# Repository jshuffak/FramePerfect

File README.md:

# FramePerfect
Code for using a Freescale 9S12C32 to intercept a GameCube controller's signal and replace it with a macro.

Project demonstration video is coming soon.

Code is contained in the folder: Gamecube_Project_Triggered/Sources/

Hardware code is contained in the folder: Output Test/GAL/ 

Special thanks to team members Kyle Diekhoff, Eric Colter, and Diego De La Fuente for pulling this one off and placing 2nd place in the Purdue Spark Challenge.

See https://engineering.purdue.edu/ECESS/spark/ for more information about the bi-annual competition hosted at Purdue University.

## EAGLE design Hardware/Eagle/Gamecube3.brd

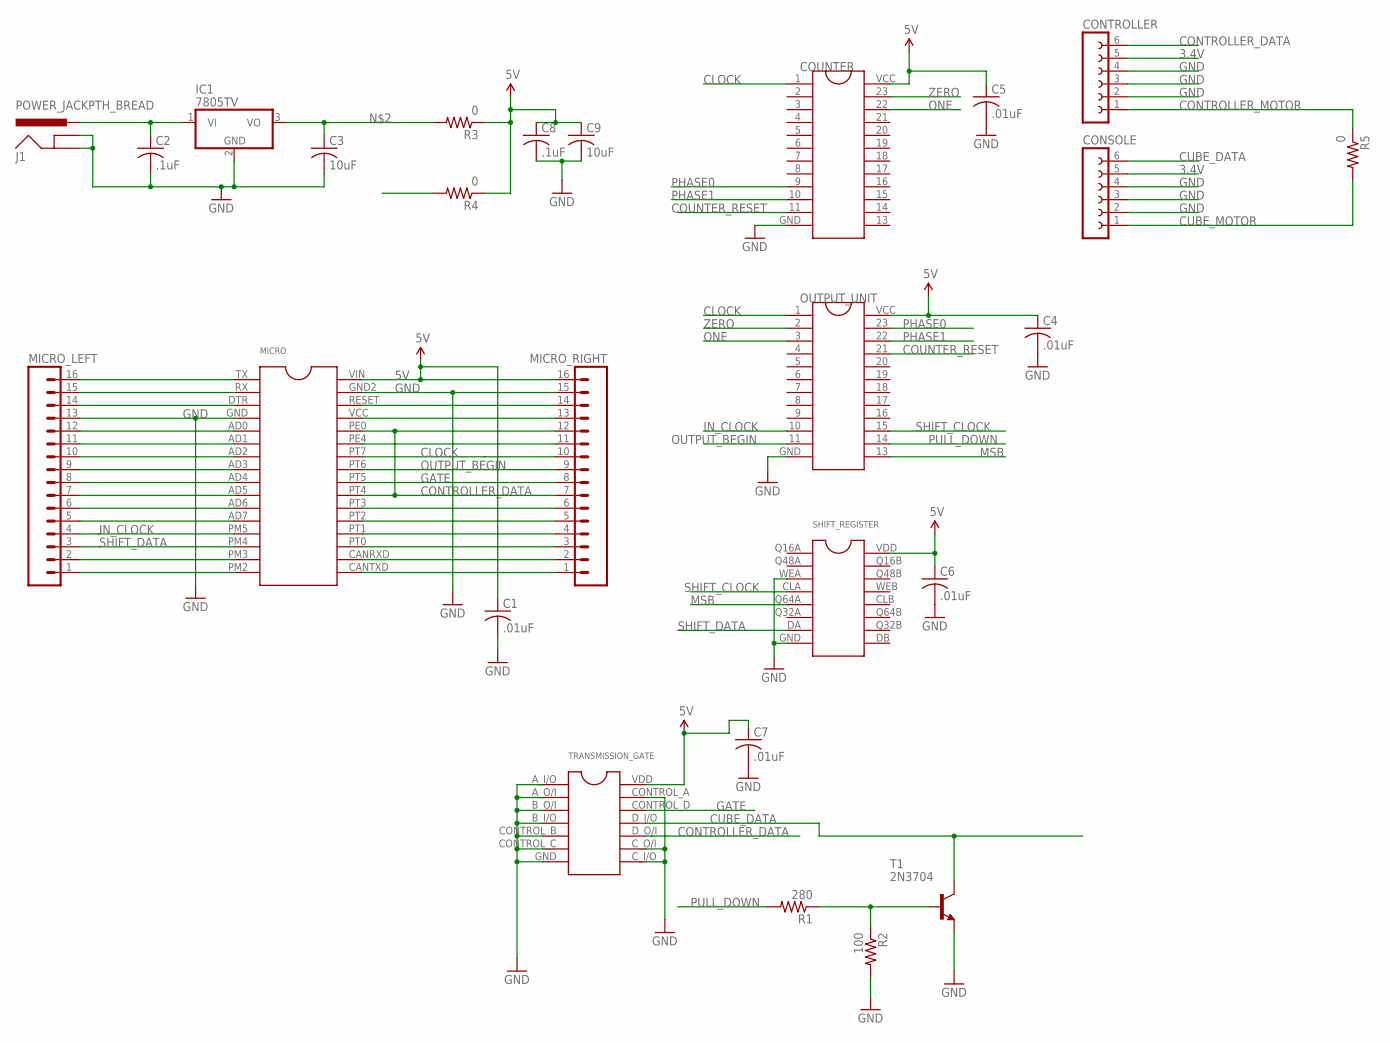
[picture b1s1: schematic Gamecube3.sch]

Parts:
C1, C4, C5, C6, C7: .01uF; C0805
C2, C8: .1uF; C0805
C3, C9: 10uF; C1206
CONSOLE: FE06-1; FE06
CONTROLLER: FE06-1; FE06
COUNTER: GAL22V10; 24-PIN-DIP
IC1: 7805TV; TO220V
J1: POWER_JACKPTH_BREAD; POWER_JACK_PTH_BREAD
MICRO: 9S12C32; 9S12-32PIN-DIP
MICRO_LEFT: M16; 16P
MICRO_RIGHT: M16; 16P
OUTPUT_UNIT: GAL22V10; 24-PIN-DIP
R1: 280; 0204/7
R2: 100; 0204/7
R3, R4, R5: 0; 0204/7
SHIFT_REGISTER: CD4517B
T1: 2N3704; TO92
TRANSMISSION_GATE: CD4066B

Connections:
3.4V: CONSOLE.5, CONTROLLER.5
5V: C1.1, C4.1, C5.1, C6.1, C7.1, C8.1, C9.1, COUNTER.VCC, MICRO.VIN, MICRO_RIGHT.16, OUTPUT_UNIT.VCC, R3.1, R4.1, SHIFT_REGISTER.VDD, TRANSMISSION_GATE.VDD
CLOCK: COUNTER.1, MICRO.PT7, MICRO_RIGHT.10, OUTPUT_UNIT.1
CONTROLLER_DATA: CONTROLLER.6, MICRO.PE0, MICRO.PT4, MICRO_RIGHT.7, MICRO_RIGHT.12, TRANSMISSION_GATE.D_O/I
CONTROLLER_MOTOR: CONTROLLER.1, R5.1
COUNTER_RESET: COUNTER.11, OUTPUT_UNIT.21
CUBE_DATA: CONSOLE.6, T1.2 (C), TRANSMISSION_GATE.D_I/O
CUBE_MOTOR: CONSOLE.1, R4.2, R5.2
GATE: MICRO.PT5, MICRO_RIGHT.8, TRANSMISSION_GATE.CONTROL_D
GND: C1.2, C2.2, C3.2, C4.2, C5.2, C6.2, C7.2, C8.2, C9.2, CONSOLE.2, CONSOLE.3, CONSOLE.4, CONTROLLER.2, CONTROLLER.3, CONTROLLER.4, COUNTER.GND, IC1.2 (GND), J1.GND, J1.GNDBREAK, MICRO.GND, MICRO.GND2, MICRO_LEFT.13, MICRO_RIGHT.15, OUTPUT_UNIT.GND, R2.2, SHIFT_REGISTER.GND, SHIFT_REGISTER.WEA, T1.3 (E), TRANSMISSION_GATE.A_I/O, TRANSMISSION_GATE.A_O/I, TRANSMISSION_GATE.B_I/O, TRANSMISSION_GATE.B_O/I, TRANSMISSION_GATE.CONTROL_A, TRANSMISSION_GATE.CONTROL_B, TRANSMISSION_GATE.CONTROL_C, TRANSMISSION_GATE.C_I/O, TRANSMISSION_GATE.C_O/I, TRANSMISSION_GATE.GND
IN_CLOCK: MICRO.PM5, MICRO_LEFT.4, OUTPUT_UNIT.10
MSB: OUTPUT_UNIT.13, SHIFT_REGISTER.Q64A
unnamed: C2.1, IC1.1 (VI), J1.PWR
unnamed: C3.1, IC1.3 (VO), R3.2
unnamed: R1.1, R2.1, T1.1 (B)
unnamed: MICRO.CANTXD, MICRO_RIGHT.1
unnamed: MICRO.PM2, MICRO_LEFT.1
unnamed: MICRO.PM3, MICRO_LEFT.2
unnamed: MICRO.AD7, MICRO_LEFT.5
unnamed: MICRO.AD6, MICRO_LEFT.6
unnamed: MICRO.AD5, MICRO_LEFT.7
unnamed: MICRO.AD4, MICRO_LEFT.8
unnamed: MICRO.AD3, MICRO_LEFT.9
unnamed: MICRO.AD2, MICRO_LEFT.10
unnamed: MICRO.AD1, MICRO_LEFT.11
unnamed: MICRO.AD0, MICRO_LEFT.12
unnamed: MICRO.DTR, MICRO_LEFT.14
unnamed: MICRO.RX, MICRO_LEFT.15
unnamed: MICRO.TX, MICRO_LEFT.16
unnamed: MICRO.CANRXD, MICRO_RIGHT.2
unnamed: MICRO.PT0, MICRO_RIGHT.3
unnamed: MICRO.PT1, MICRO_RIGHT.4
unnamed: MICRO.PT2, MICRO_RIGHT.5
unnamed: MICRO.PT3, MICRO_RIGHT.6
unnamed: MICRO.PE4, MICRO_RIGHT.11
unnamed: MICRO.VCC, MICRO_RIGHT.13
unnamed: MICRO.RESET, MICRO_RIGHT.14
ONE: COUNTER.22, OUTPUT_UNIT.3
OUTPUT_BEGIN: MICRO.PT6, MICRO_RIGHT.9, OUTPUT_UNIT.11
PHASE0: COUNTER.9, OUTPUT_UNIT.23
PHASE1: COUNTER.10, OUTPUT_UNIT.22
PULL_DOWN: OUTPUT_UNIT.14, R1.2
SHIFT_CLOCK: OUTPUT_UNIT.15, SHIFT_REGISTER.CLA
SHIFT_DATA: MICRO.PM4, MICRO_LEFT.3, SHIFT_REGISTER.DA
ZERO: COUNTER.23, OUTPUT_UNIT.2

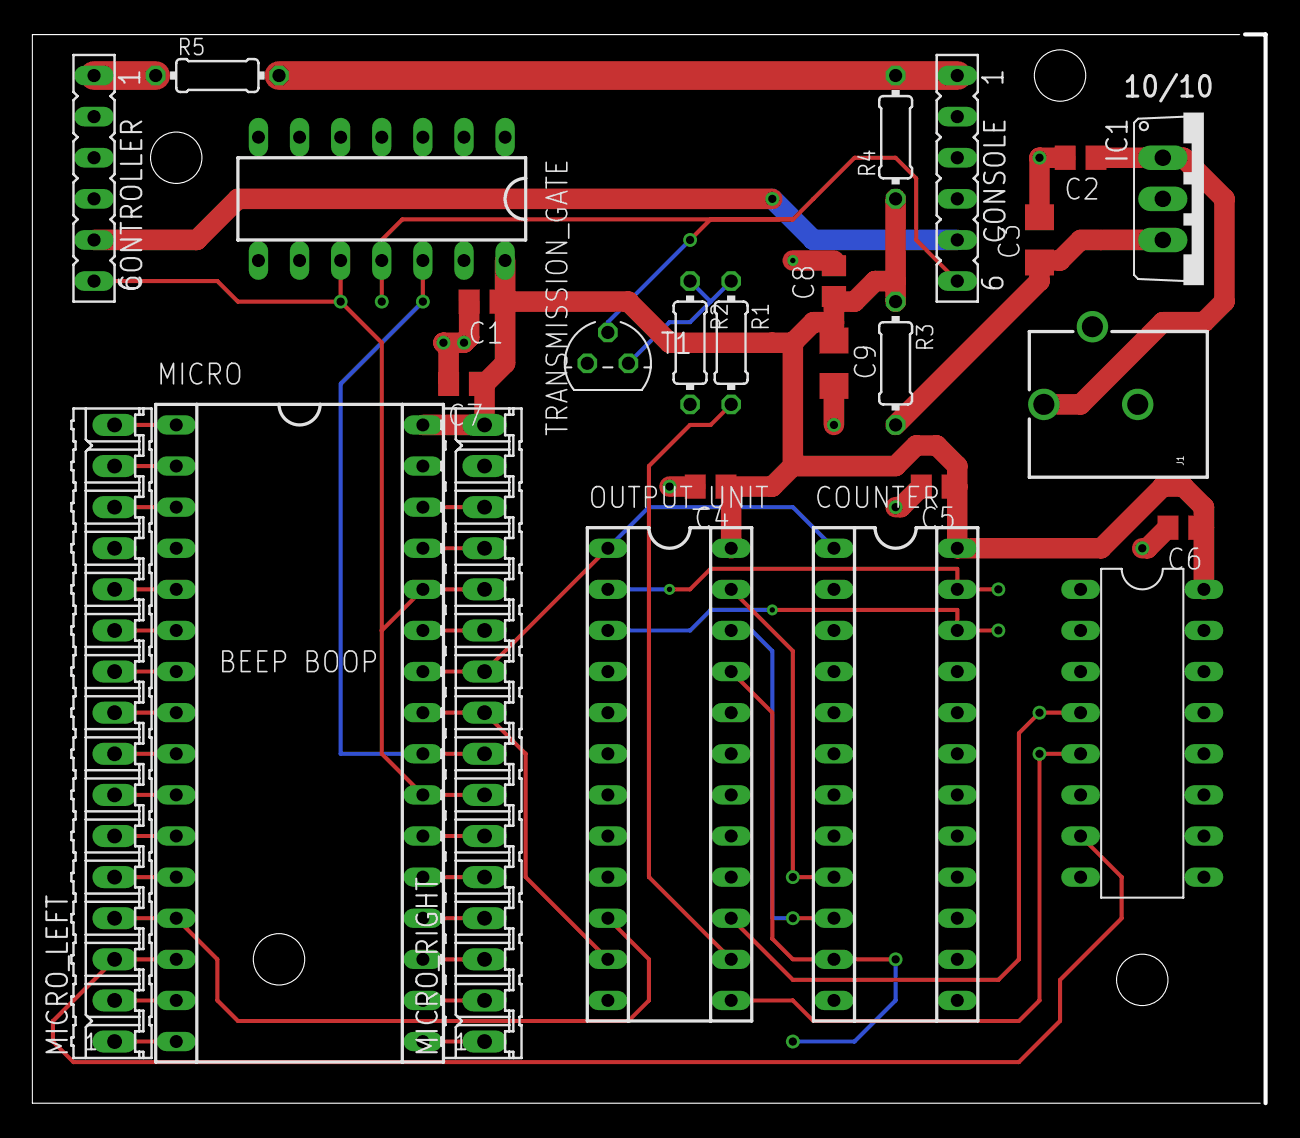
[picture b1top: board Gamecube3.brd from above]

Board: 2 copper layers, 76.1 x 66.0 mm, 26 parts (0 on the bottom side), 45 nets.

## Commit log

2015-11-21 Added some sample structure files to the repo.
2015-11-26 A whole bunch of stuff. Neat!
2015-12-04 Added some GAL stuff and also the working echo program.
2015-12-04 Added all necessary files to the repo and added them to the CodeWarrior project.
2015-12-04 Added some initializations and finished macro.h
2015-12-04 Changed some stuff
2015-12-04 Changed some more stuff aparently
2015-12-04 Added functions to microcontroller.h that are needed by other modules
2015-12-05 changes to the code warrior project i dont actually want to keep.
2015-12-05 Update macro.c
    Kyle did the best job ever made in the world
2015-12-05 Change define
    Rickster the fan man
2015-12-05 Added equals sign for macro
2015-12-05 Update macro.h
    Fixed macro.h
2015-12-05 Finished the definitions of the .h files and some definitions in the .c files.
2015-12-05 Changed Structure to multi macro
2015-12-05 The horrible length update
2015-12-05 Added defined start of each macro
2015-12-05 Changed scheme.h to not have definitions of each scheme and moved them to scheme.c.
2015-12-05 Update microcontroller.c
    - Changes to line up controller/console output with IRQ and to make sure that it's length of time was good.
2015-12-05 Finished main.
2015-12-05 Added scheme.c to the codewarrior project and fixed a bug to let it compile.
2015-12-05 Shut up nerd
2015-12-05 fox jump
2015-12-05 Tested Kyle's Code with control.h functionality and it seems to work. Also reconfigured scheme1 to use some niftey macros.
2015-12-05 Forgot to change back the changes I made to test.
2015-12-05 Changed CYCLESFOR40MICROWAIT to ensure that the micro is waiting 40 microseconds.
2015-12-05 Added Kyle's Macro generator into the repo.
2015-12-05 Added Colter's work into the repo.
2015-12-07 Updated the repo with the merged changes from Colter and Diego's work.
2015-12-07 Fixed a bug in the macro.c file.
2015-12-07 Changed the routine to mask the left and right slider values when the macro button is pressed.
2015-12-07 Now masks the x and y joystick values when the macro button is pressed unless they cross the x and y thresholds.
2015-12-07 Changed the thresholds to be a snappier value.
2015-12-07 Added a watchdog timer to the micro to ensure that the protocol is working properly.
2015-12-07 Refixed a debugging problem and added an initial state of input.
2015-12-07 Change initial bit
    ye
2015-12-07 do you have the time to listen to me whine.
2015-12-07 4 scores and seven years ago our founding fathers
    did stuff
2015-12-07 Schemes are updated
2015-12-07 Updated initial bits sent to GAL
    Updated the initial bits to be blank inputs so that the GAL doesn't output garbage initially.
2015-12-07 True to its name
2015-12-07 12/7/2015: Updated and Added Macros
2015-12-07 Update and Added Macros 12/7/2015
2015-12-07 12/7/2015: Updated and Added Schemes
2015-12-08 Assert macro frames 2 times
    Changed the macro so that each frame is asserted 2 times instead of 3.
2015-12-08 Updated a couple of macros
    Updated some macros with the new 2 input frame per game frame protocol.
2015-12-08 Updated some more macros
    Updated some macros with new sizes.
2015-12-08 Added masks to the joystick
2015-12-08 updated macro.c to have macros. limited RAM
2015-12-08 updated macro.h 12/8/2015 1:21 am. limited RAM
2015-12-08 Using flash memory?
    Hopefully using flash memory now.
2015-12-09 Added drillshine. Test1
2015-12-09 added drillshine to scheme1 x-z
2015-12-09 updated drillshine macro8
2015-12-09 update macro.h for drill
2015-12-09 DRILL 2
2015-12-09 DRILL2
2015-12-09 DRILL 3
2015-12-09 Commiting broken DrillShine
    Broken drill shine
2015-12-09 final fox macros
2015-12-09 update macro.h full fox
2015-12-11 macro.c updated
    update
2015-12-11 macro.h updated
    more fun stuff
2015-12-11 Pinout changed to work on PCB
2015-12-11 Ready for Spark Challenge!
2016-01-16 These were the last changes made to submit the project for grading in ECE 362.
2016-06-11 Added Eagle files

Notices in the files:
parts and their libraries:
SparkFun-Connectors: Licensing: Creative Commons ShareAlike 4.0 International - https://creativecommons.org/licenses/by-sa/4.0
